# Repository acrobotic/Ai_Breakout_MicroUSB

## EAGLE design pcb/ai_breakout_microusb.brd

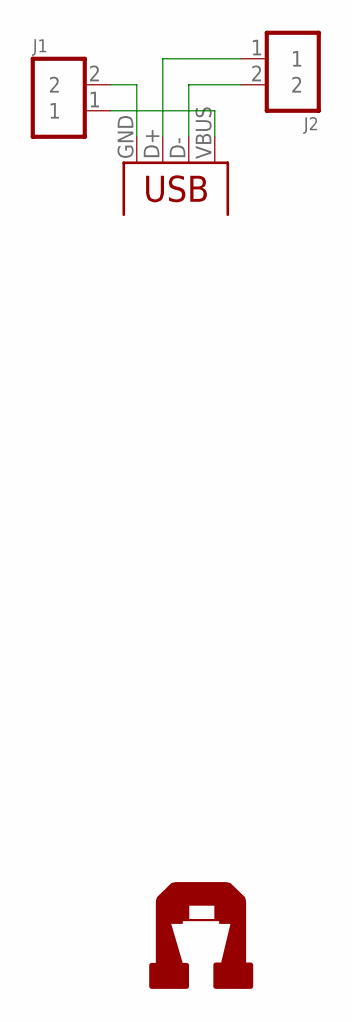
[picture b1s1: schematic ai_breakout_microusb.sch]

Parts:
J1: 1X02
J2: 1X02NOFIRST; 1X02-NOFIRST
U$2: AI-LOGOXS; AI-LOGO-XS
USB1: USBMICROB-TH; USB-MICROB-TH

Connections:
D+: J2.1, USB1.D+
D-: J2.2, USB1.D-
GND: J1.2, USB1.GND
VBUS: J1.1, USB1.VBUS

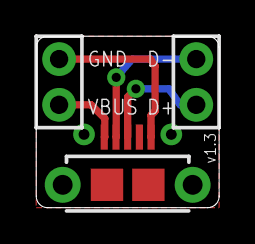
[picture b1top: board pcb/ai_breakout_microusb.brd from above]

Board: 2 copper layers, 10.2 x 9.5 mm, 4 parts (1 on the bottom side), 4 nets.

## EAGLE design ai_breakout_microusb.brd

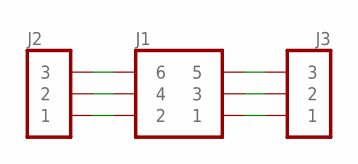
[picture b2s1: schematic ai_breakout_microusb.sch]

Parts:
J1: 2X03
J2: 1X03NOFIRST; 1X03-NOFIRST
J3: 1X03

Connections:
unnamed: J1.1, J3.1
unnamed: J1.3, J3.2
unnamed: J1.5, J3.3
unnamed: J1.2, J2.1
unnamed: J1.4, J2.2
unnamed: J1.6, J2.3

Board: 2 copper layers, 4 parts (1 on the bottom side), 6 nets, no tracks yet.

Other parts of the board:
U$1: AI-LOGO-XS

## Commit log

2014-10-20 redesigned to DIL form factor
2014-10-20 updated silkscreen
2014-10-21 ready for manufacturing
2014-11-03 udpated to 2-pin version
